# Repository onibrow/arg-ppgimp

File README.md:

# Arias Research Group - PPG & Impedence Measurement

## Seiya Ono Sp'19

The goal of this project is to collaborate with doctors at UCSD and Dr. Muller's student, Sina Faraji, to create a test bench for our group's Bioimpedence Array and OLED/OPD Oxymeter sensors to measure tissue damage in mice. We hope to use Sina Faraji's new OLED/OPD driver chip to take PPG measurements while using our own impedence arrays and electronics to measure tissue of the target.

-----

## Specs

- 1 PPG Sensor
    - 1 Red OLED
    - 1 NIR OLED
    - 1 OPD
    - Sina's Driver Chip
- 15 Impedence Electrodes
    - Impedence measurement AFE
    - Current Driver (200uA to 700uA, up to 1mA)
    - 15 to 2 selection mux
- 9V Power
- Coms over Serial

### PPG Sensor

Sina's OLED/OPD Driver Amplifier has the capability to driver 8 pairs of OLEDs and take readings from 8 OPDs. It handles all the amplification through SPI programmable registers. The closed loop in the transimpedence amplifiers can help get rid of any DC components in the OPD readings. It runs off of 1.1V digital logic, and 8V driver power.

If his chip does not go well, we will implement our own OLED drivers and OPD transimpedence amplifiers.

### Impedence Electrodes

We were asked to get our 15 electrode array to be able to take any impedence measurement between any two user selectable electrodes, while also being able to select any two electrodes to drive with a set amount of current. This divides this part of the board into three distance parts - the multiplexor selection and configuration, tunable current source, and impdence measurement. The following section will outline the different chip selection and their respective specs.

#### Multiplexor

Because the board is spec'd to be able to take impedence measurements as well as source current, it is critical to choose a multiplexor that has very low on resistance, while having very high off resistance. Luckily, most CMOS technology has this as standard, so picking an analog mux was not very difficult. We settled with the [ADG1608/1609](https://www.analog.com/en/products/adg1608.html) because of its 3 bit (8 input) mux, as well as its secondary variant 2 bit (4x2 input) DPDT (double pole double throw) configuration. To differentiate, the ADG1608 variant is the 3 bit 8 input mux, and the ADG1609 is the 2 bit 4x2 input mux. See the figure below for clarification.

By using two pairs of ADG1608's, a 16x2 input 1x2 output can be created. This means the circuit can individually select a pair of electrodes to be used by the impedence analyzer and tunable current source. To select between either of the two inputs, the ADG1609 will be used as a demuxer to select either the impedence analyzer or tunable current source. The DPDT configuration is very usedful in this sceneario because we are trying to always drive a _pair_ of electrodes. Here are some important specs when running off of a 3.3V power rail.

| Parameter | Value | Unit |
| --------- | ----- | ---- |
| R\_on      | 13.5  | Ohms |
| S/D Leakage | 0.1 | nA max |
| -3dB 1608 | 34 | MHz typ |
| -3dB 1609 | 72 | MHz typ |
| C\_S OFF | 23 | pF typ |
| C\_D OFF 1608 | 145 | pF type |
| C\_D OFF 1609 | 72 | pF typ |
| C\_S/D ON 1608 | 173 | pF typ |
| C\_S/D ON 1609 | 95 | pF typ |
| I\_DD | 0.001 | uA typ |
| V\_DD | 3.3 | V |
|I\_S/D 1608 | 126 | mA max |
|I\_S/D 1609 | 94 | mA max |

As we are dealing with specimens in the 10K Ohm range, the 13.5 Ohm and 173pF ON impedence is negligible, even if the electrode is traveling through 2 multiplexors. The max available current draw is much over the required 1mA of current through the electrodes, so the chip fits our needs. It aslo fits our impedance chip bandwidth, where it can do frequency sweeps over 1kHz to 100kHz. More on this in the "Impedence Analyzer" section.

#### Tunable Current Source

In order to drive our selectable electrodes with a user defined amount of current, we needed an adjustable current source. For this task, the [LM134/LM234/LM334 3-Terminal Adjustable Current Source](http://www.ti.com/product/LM134) was chosen. Specifically, the LM334 was chosen for its small form factor and easily identifiable 3-Pin Through Hole casing. It has a huge operating voltage from 1V to 40V, and can be tuned to supply current between 1uA to 10mA. The chip can also be operated in a temperature compensation region to eliminate its temperature dependence up to 0.2% accuracy.

For this circuit, the diode to use was already suggested, so the next choice was to pick out a digital potentiometer. TI also provided the math to prove the temperature coefficient compensation with the chosen diode, and drew the following relationship between R1 and R2:

From this, 1k and 10k 256 step digital potentiometers were chosen, with the math coming out to 3.9/39 Ohms per step, capable of driving in the range of 67.7uA to just short of 1mA. This just about fits our spec, going over to the upper limit of 1mA. The digital potentiometers chosen are the [AD8400](https://www.analog.com/en/products/ad8400.html) in both the 1K and 10K variant. They are controlled over SPI as designated write only slave devices. It can operate at between 3V and 5.5V and will typically draw less than 1mA.

#### Impedence Measurements

We would like to measure impedences between 1M Ohm (Magnitude) and 1k Ohm on our species. The chip for this is the [AD5933](https://www.analog.com/en/products/ad5933.html) which can do frequency sweeps. See Page 14 of the Data Sheet for more information on how to program the chip to do this.

Setting Gain - See Page 18 on how to choose the Gain setting resistor R\_FB to ensure that the analog readings do not saturate. The gain factor needs to be recalculated if R\_FB changes, if the output excitation voltage (more on this later) changes, or if the PGA gain is set differently. On the topic of operating voltages, there are 4 to choose from:

| Range | Output Excitation Voltage Amplitude | Output DC Bias Level | Output Series Resistance |
| ----- | ----------------------------------- | -------------------- | ------------------------ |
| 1 | 1.98 V p-p | 1.48 V | 200 Ohm |
| 2 | 0.97 V p-p | 0.76 V | 2.4k Ohm |
| 3 | 383 mV p-p | 0.31 V | 1.0k Ohm |
| 4 | 198 mV p-p | 0.173 V| 600 Ohm |

These numbers factor into what value should be chosen for the feedback resistor. The equation for choosing the feedback resistor is as follows:

Output Excitation Voltage Range * Gain Setting Resistor / Z\_Uknown * PGA Gain

By selecting the typical range 1 (~2V p-p) setting, we must choose a R\_FB that is roughly on the same order of magnitude as the unknown impedences we are measuring. From Yasser's Ulcer sensing paper (Swisher, S. L. et al. Impedance sensing device enables early detection of pressure ulcers in vivo. Nat. Commun. 6:6575 doi: 10.1038/ncomms7575 (2015)), we find that the typical impedence magnitude ranges from 10^4 to 10^6, so we will choos a 1M Ohm resistor for the feedback. This way, it should be able to cover a very wide range of impedences.

The chip does come with an internal 16.776 MHz oscillator, but it can be replaced by placing a 16MHz oscillator on MCLK, and then setting the control register to use the external clock. By default, on power up the internal oscillator is selected.

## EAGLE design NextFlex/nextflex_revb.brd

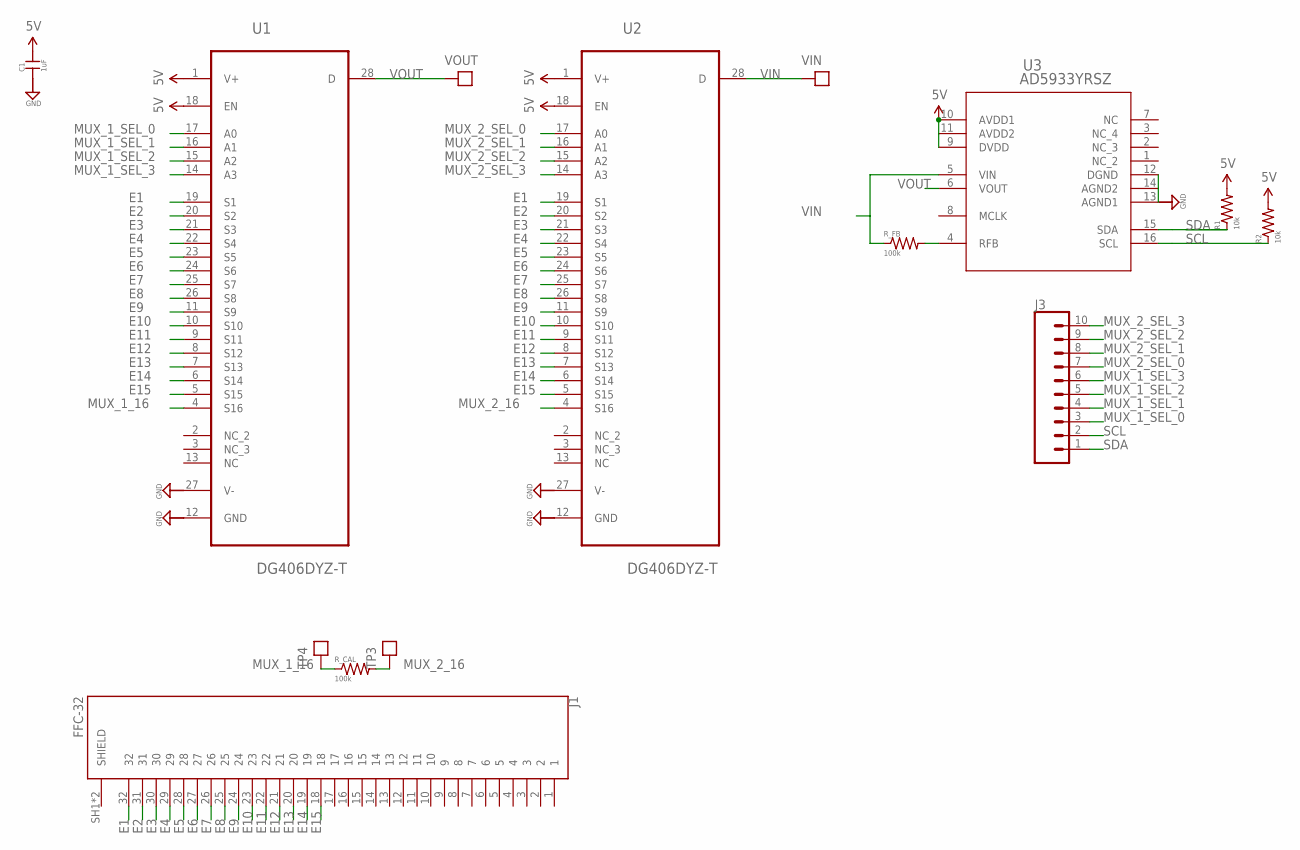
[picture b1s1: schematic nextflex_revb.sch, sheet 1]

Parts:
C1: 1uF; 0603-CAP
J1: FFC-32; MOLEX_503480-3200
J3: CONN_10"; 1X10
R1, R2: 10k; 0603-RES
R_CAL: 100k; 0603-RES
R_FB: 100k; 0603-RES
TP3, TP4: TEST_POINTTHRU; TEST_POINT
U1, U2: DG406DYZ-T; SOIC127P1032X265-28N
U3: AD5933YRSZ; RS_16
VIN: TEST_POINTTHRU; TEST_POINT
VOUT: TEST_POINTTHRU; TEST_POINT

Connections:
5V: C1.2, R1.2, R2.2, U1.1 (V+), U1.18 (EN), U2.1 (V+), U2.18 (EN), U3.9 (DVDD), U3.10 (AVDD1), U3.11 (AVDD2); also elsewhere on the board
E1: J1.32, U1.19 (S1), U2.19 (S1)
E2: J1.31, U1.20 (S2), U2.20 (S2)
E3: J1.30, U1.21 (S3), U2.21 (S3)
E4: J1.29, U1.22 (S4), U2.22 (S4)
E5: J1.28, U1.23 (S5), U2.23 (S5)
E6: J1.27, U1.24 (S6), U2.24 (S6)
E7: J1.26, U1.25 (S7), U2.25 (S7)
E8: J1.25, U1.26 (S8), U2.26 (S8)
E9: J1.24, U1.11 (S9), U2.11 (S9)
E10: J1.23, U1.10 (S10), U2.10 (S10)
E11: J1.22, U1.9 (S11), U2.9 (S11)
E12: J1.21, U1.8 (S12), U2.8 (S12)
E13: J1.20, U1.7 (S13), U2.7 (S13)
E14: J1.19, U1.6 (S14), U2.6 (S14)
E15: J1.18, U1.5 (S15), U2.5 (S15)
GND: C1.1, U1.12 (GND), U1.27 (V-), U2.12 (GND), U2.27 (V-), U3.12 (DGND), U3.13 (AGND1), U3.14 (AGND2); also elsewhere on the board
MUX_1_16: R_CAL.1, TP4.1, U1.4 (S16)
MUX_1_SEL_0: J3.3, U1.17 (A0); also elsewhere on the board
MUX_1_SEL_1: J3.4, U1.16 (A1); also elsewhere on the board
MUX_1_SEL_2: J3.5, U1.15 (A2); also elsewhere on the board
MUX_1_SEL_3: J3.6, U1.14 (A3); also elsewhere on the board
MUX_2_16: R_CAL.2, TP3.1, U2.4 (S16)
MUX_2_SEL_0: J3.7, U2.17 (A0); also elsewhere on the board
MUX_2_SEL_1: J3.8, U2.16 (A1); also elsewhere on the board
MUX_2_SEL_2: J3.9, U2.15 (A2); also elsewhere on the board
MUX_2_SEL_3: J3.10, U2.14 (A3); also elsewhere on the board
unnamed: R_FB.2, U3.4 (RFB)
SCL: J3.2, R2.1, U3.16 (SCL); also elsewhere on the board
SDA: J3.1, R1.1, U3.15 (SDA); also elsewhere on the board
VIN: R_FB.1, U2.28 (D), U3.5 (VIN), VIN.1
VOUT: U1.28 (D), U3.6 (VOUT), VOUT.1

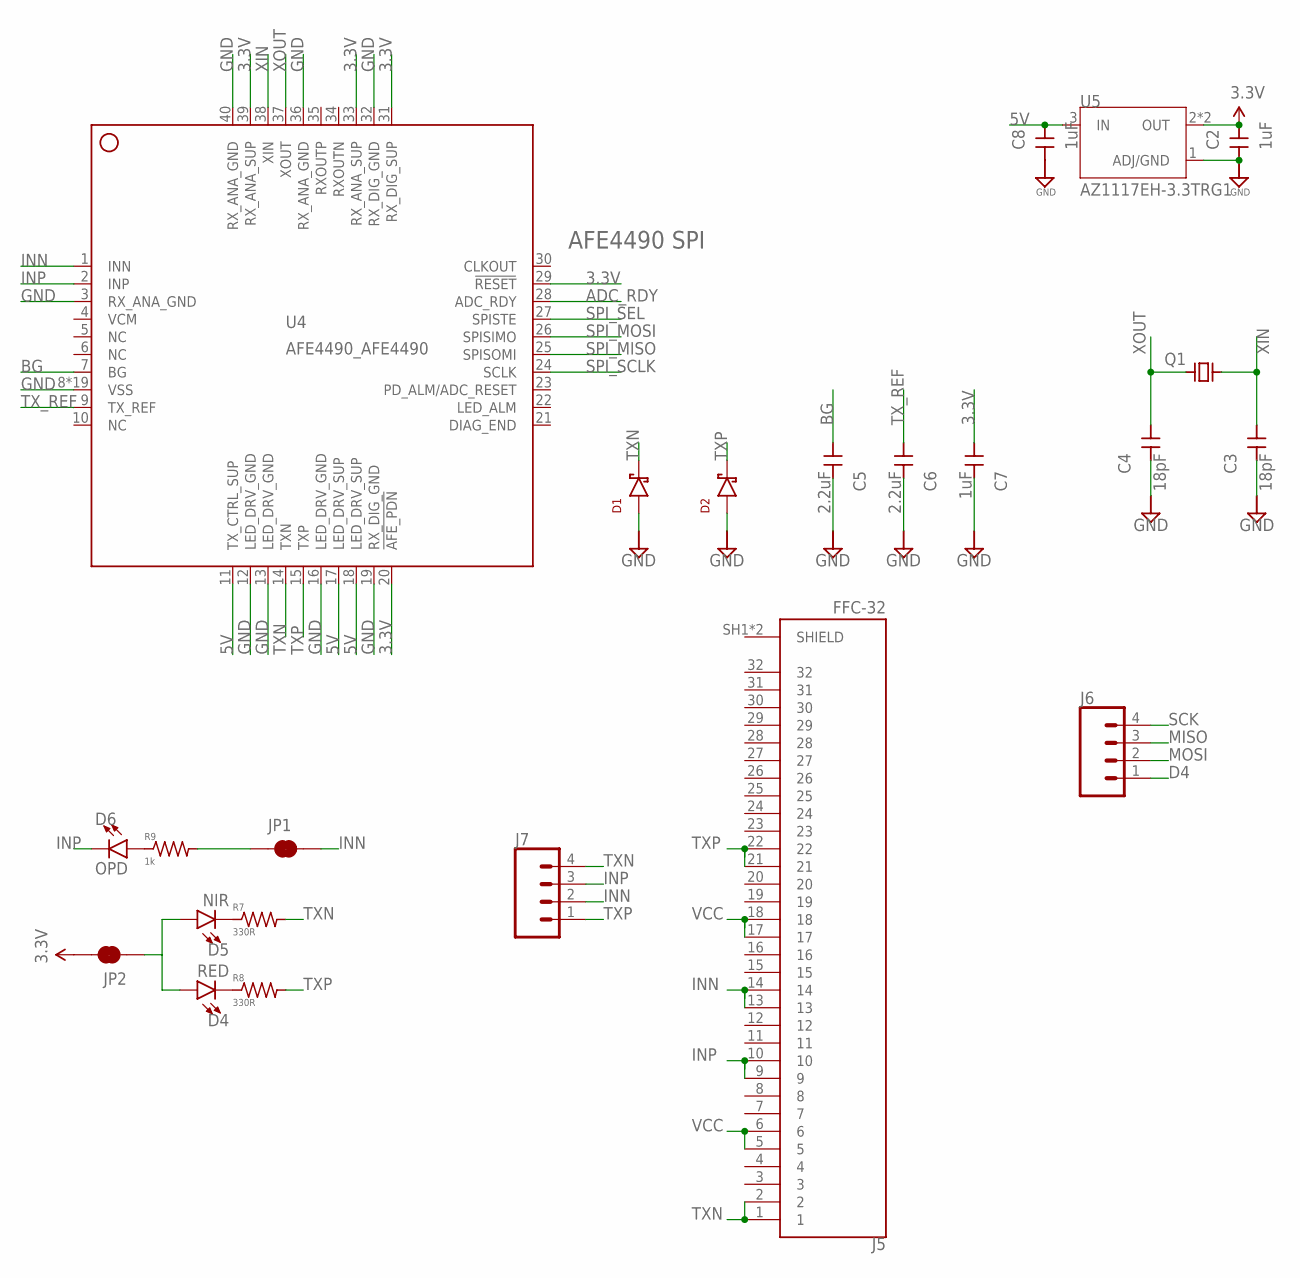
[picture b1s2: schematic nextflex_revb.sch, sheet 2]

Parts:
C2, C7, C8: 1uF; 0603-CAP
C3, C4: 18pF; 0603-CAP
C5, C6: 2.2uF; 0603-CAP
D1, D2: DIODE_CZRU; CZRU
D4: RED; LED-0603
D5: NIR; LED-0603
D6: OPD; LED-1206
J5: FFC-32; MOLEX_503480-3200
J6, J7: CONN_04; 1X04
JP1, JP2: JUMPER-SMT_2_NC_TRACE_NO-SILK; SMT-JUMPER_2_NC_TRACE_NO-SILK
Q1: CRYSTAL_SMOL; XTAL500X320X130N
R7, R8: 330R; 0603-RES
R9: 1k; 0603-RES
U4: AFE4490_AFE4490; AFE4490_QFN40-6X6
U5: AZ1117EH-3.3TRG1; SOT230P700X180-4N

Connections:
3.3V: C2.1, C7.1, JP2.2, U4.20 (!AFE_PDN), U4.29 (!RESET), U4.31 (RX_DIG_SUP), U4.33 (RX_ANA_SUP), U4.39 (RX_ANA_SUP), U5.2 (OUT), U5.4 (OUT); also elsewhere on the board
5V: C8.1, U4.11 (TX_CTRL_SUP), U4.17 (LED_DRV_SUP), U4.18 (LED_DRV_SUP), U5.3 (IN); also elsewhere on the board
ADC_RDY: U4.28 (ADC_RDY)
BG: C5.1, U4.7 (BG)
D4: J6.1; also elsewhere on the board
GND: C2.2, C3.2, C4.2, C5.2, C6.2, C7.2, C8.2, D1.P, D2.P, U4.3 (RX_ANA_GND), U4.8 (VSS), U4.12 (LED_DRV_GND), U4.13 (LED_DRV_GND), U4.16 (LED_DRV_GND), U4.19 (RX_DIG_GND), U4.32 (RX_DIG_GND), U4.36 (RX_ANA_GND), U4.40 (RX_ANA_GND), U4.EXP@1 (VSS), U4.EXP@2 (VSS), U4.EXP@3 (VSS), U4.EXP@4 (VSS), U4.EXP@5 (VSS), U4.EXP@6 (VSS), U4.EXP@7 (VSS), U4.EXP@8 (VSS), U4.EXP@9 (VSS), U4.EXP@10 (VSS), U4.EXP@11 (VSS), U4.EXP@12 (VSS), U4.EXP@13 (VSS), U4.EXP@14 (VSS), U4.EXP@15 (VSS), U4.EXP@16 (VSS), U4.PWR@1 (VSS), U4.PWR@2 (VSS), U5.1 (ADJ/GND); also elsewhere on the board
INN: J5.13, J5.14, J7.2, JP1.2, U4.1 (INN)
INP: D6.C, J5.9, J5.10, J7.3, U4.2 (INP)
MISO: J6.3; also elsewhere on the board
MOSI: J6.2; also elsewhere on the board
unnamed: D4.A, D5.A, JP2.1
unnamed: D5.C, R7.1
unnamed: D4.C, R8.1
unnamed: D6.A, R9.1
unnamed: JP1.1, R9.2
SCK: J6.4; also elsewhere on the board
SPI_MISO: U4.25 (SPISOMI); also elsewhere on the board
SPI_MOSI: U4.26 (SPISIMO); also elsewhere on the board
SPI_SCLK: U4.24 (SCLK); also elsewhere on the board
SPI_SEL: U4.27 (SPISTE); also elsewhere on the board
TXN: D1.N, J5.1, J5.2, J7.4, R7.2, U4.14 (TXN)
TXP: D2.N, J5.21, J5.22, J7.1, R8.2, U4.15 (TXP)
TX_REF: C6.1, U4.9 (TX_REF)
VCC: J5.5, J5.6, J5.17, J5.18; also elsewhere on the board
XIN: C3.1, Q1.1 (A), U4.38 (XIN)
XOUT: C4.1, Q1.2 (B), U4.37 (XOUT)

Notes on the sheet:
AFE4490 SPI

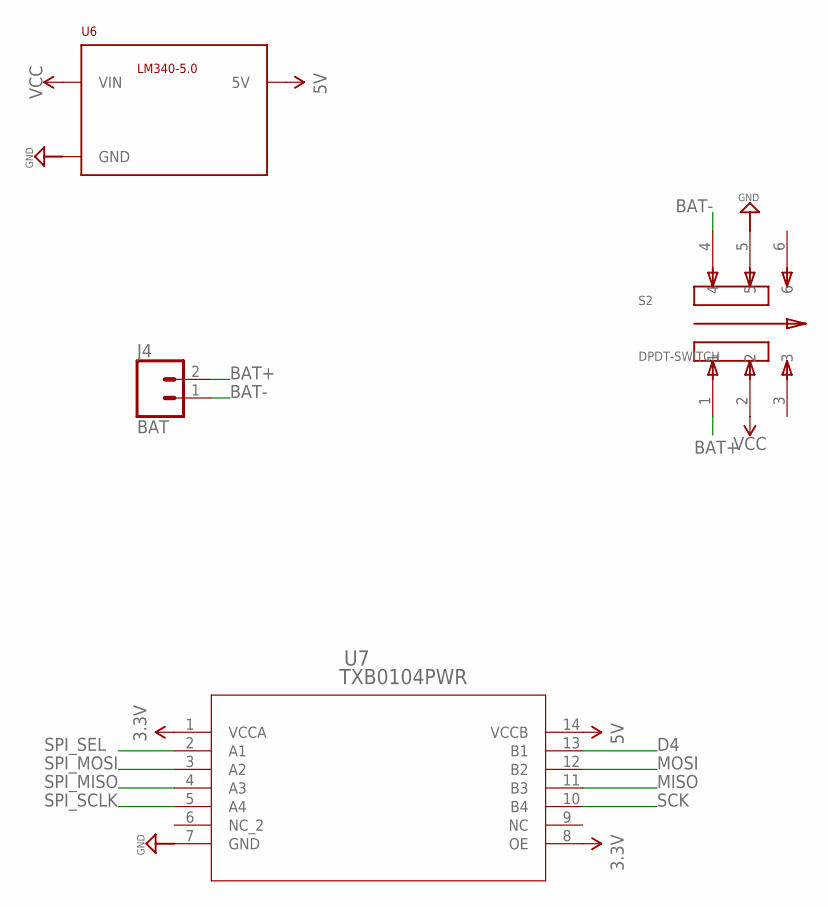
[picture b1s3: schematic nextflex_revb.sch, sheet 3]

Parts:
J4: BAT; 1X02
S2: DPDT-SWITCH; SW_JS202011SCQN
U6: LM340MPX-5.0230; SOT230P700X180-4N
U7: TXB0104PWR; PW14

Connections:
3.3V: U7.1 (VCCA), U7.8 (OE); also elsewhere on the board
5V: U6.3 (5V), U7.14 (VCCB); also elsewhere on the board
BAT+: J4.2, S2.1
BAT-: J4.1, S2.4
D4: U7.13 (B1); also elsewhere on the board
GND: S2.5, U6.2 (GND), U6.4 (GND), U7.7 (GND); also elsewhere on the board
MISO: U7.11 (B3); also elsewhere on the board
MOSI: U7.12 (B2); also elsewhere on the board
SCK: U7.10 (B4); also elsewhere on the board
SPI_MISO: U7.4 (A3); also elsewhere on the board
SPI_MOSI: U7.3 (A2); also elsewhere on the board
SPI_SCLK: U7.5 (A4); also elsewhere on the board
SPI_SEL: U7.2 (A1); also elsewhere on the board
VCC: S2.2, U6.1 (VIN); also elsewhere on the board

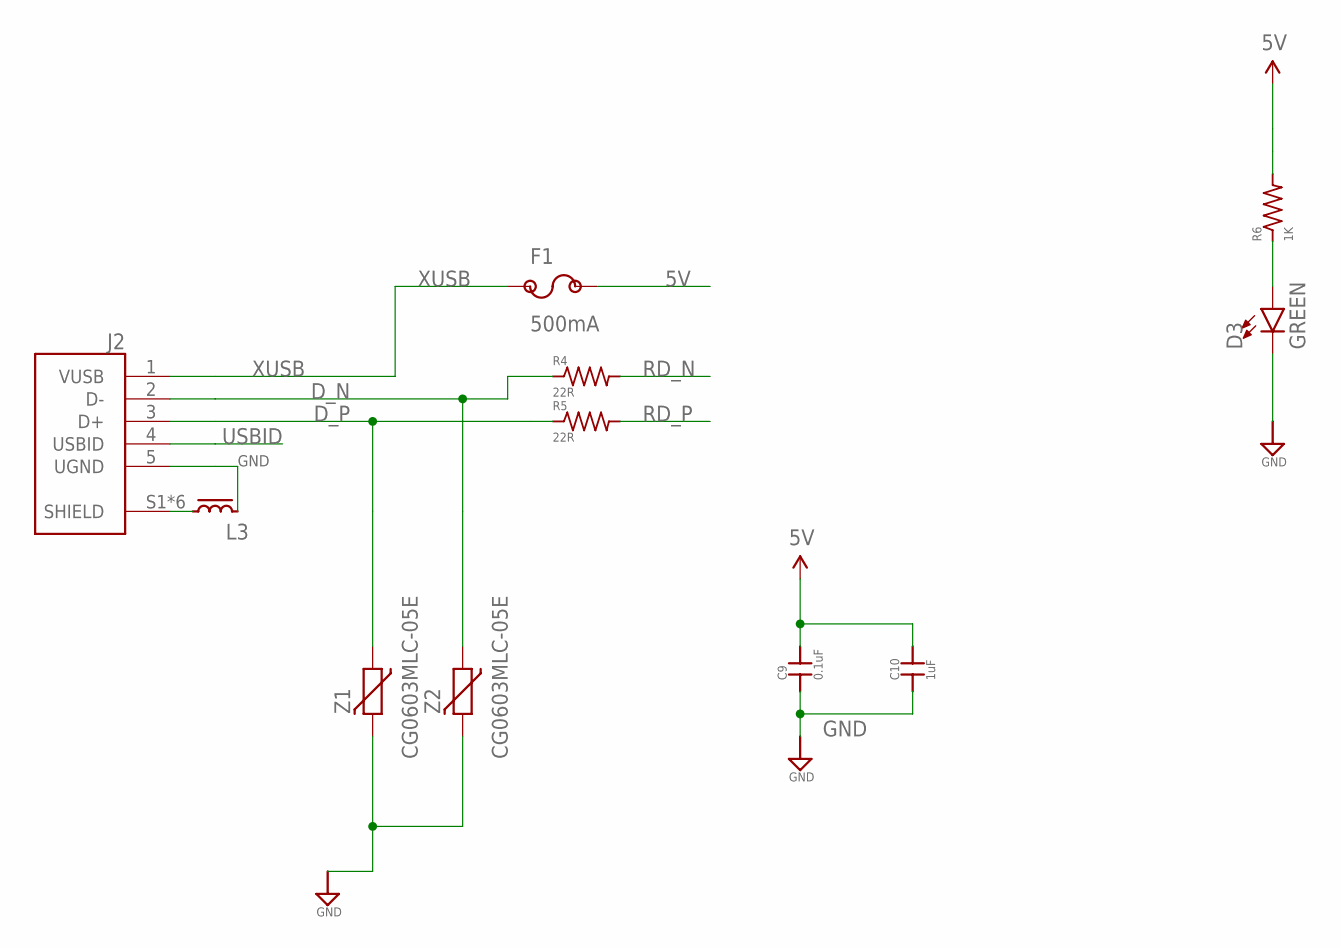
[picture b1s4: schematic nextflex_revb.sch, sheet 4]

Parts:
C9: 0.1uF; 0603-CAP
C10: 1uF; 0603-CAP
D3: GREEN; LED-0603
F1: 500mA; 1206
J2: USB; FCI_10103594-0001LF
L3: IND; IND_2012
R4, R5: 22R; 0603-RES
R6: 1K; 0603-RES
Z1, Z2: CG0603MLC-05E; 0603-RES

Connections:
5V: C9.2, C10.2, F1.2, R6.2; also elsewhere on the board
D_N: J2.2 (D-), R4.1, Z2.1
D_P: J2.3 (D+), R5.1, Z1.1
GND: C9.1, C10.1, D3.C, J2.5 (UGND), L3.2, Z1.2, Z2.2; also elsewhere on the board
unnamed: D3.A, R6.1
RD_N: R4.2; also elsewhere on the board
RD_P: R5.2; also elsewhere on the board
SHIELD: J2.S1 (SHIELD), J2.S2 (SHIELD), J2.S3 (SHIELD), J2.S4 (SHIELD), J2.S5 (SHIELD), J2.S6 (SHIELD), L3.1
USBID: J2.4 (USBID)
XUSB: F1.1, J2.1 (VUSB)

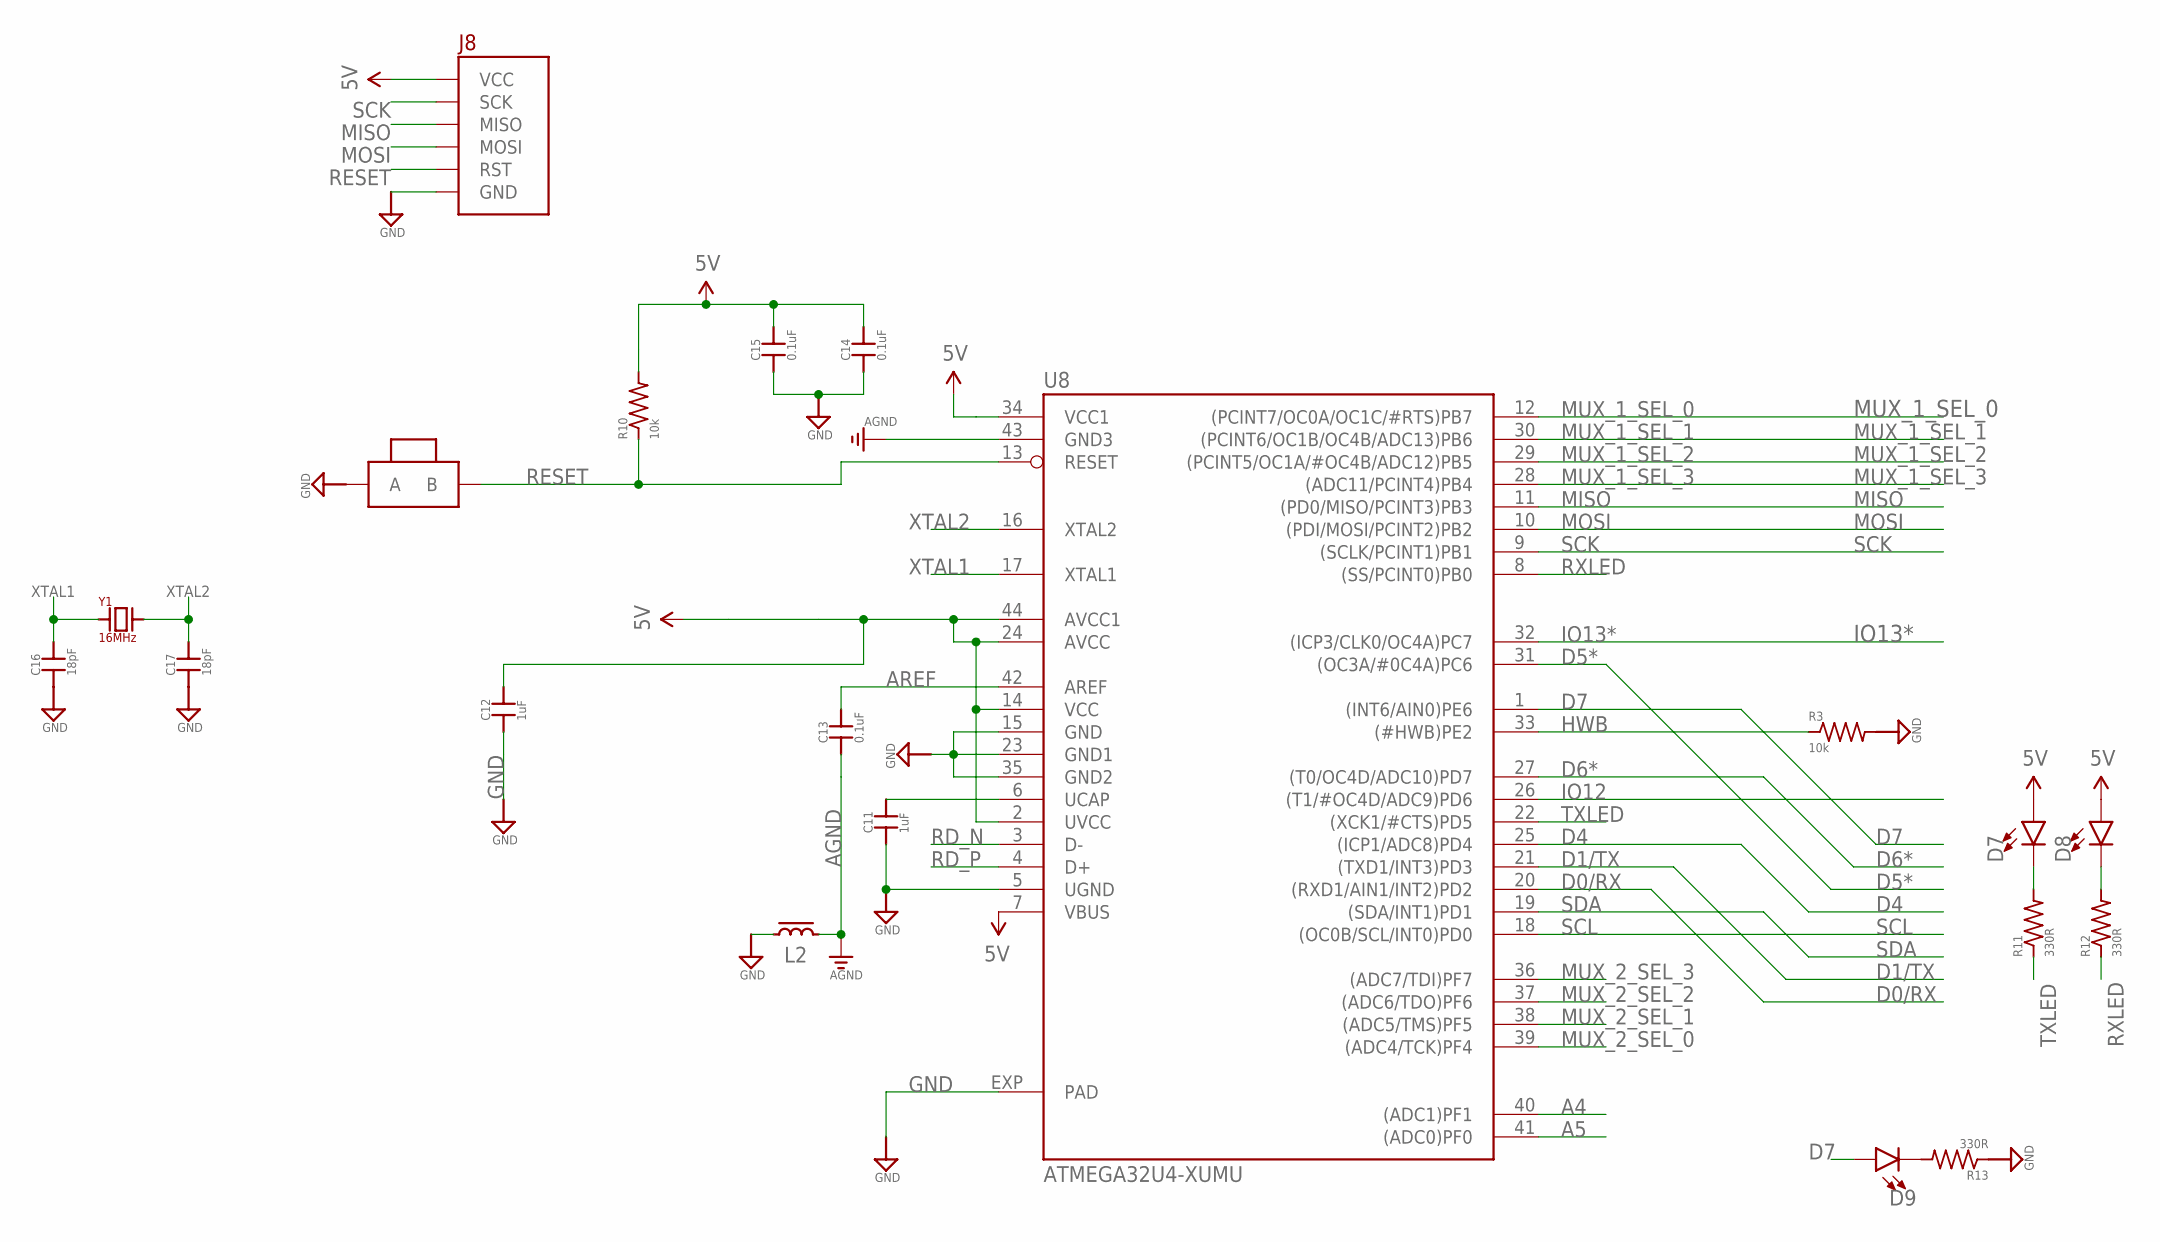
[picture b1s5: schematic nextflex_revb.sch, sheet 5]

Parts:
C11, C12: 1uF; 0603-CAP
C13, C14, C15: 0.1uF; 0603-CAP
C16, C17: 18pF; 0603-CAP
D7, D8, D9: LED0603; LED-0603
J8: BURNIN
L2: IND; IND_2012
R3, R10: 10k; 0603-RES
R11, R12, R13: 330R; 0603-RES
SW1: BTN-PTS810; BTN_PTS810
U8: ATMEGA32U4-XUMU; QFN44ML7X7
Y1: 16MHz; XTAL500X320X130N

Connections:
5V: C12.2, C14.2, C15.2, D7.A, D8.A, J8.3.3V (VCC), R10.2, U8.2 (UVCC), U8.7 (VBUS), U8.14 (VCC), U8.24 (AVCC), U8.34 (VCC1), U8.44 (AVCC1); also elsewhere on the board
A4: U8.40 ((ADC1)PF1)
A5: U8.41 ((ADC0)PF0)
AGND: C13.1, L2.2, U8.43 (GND3)
AREF: C13.2, U8.42 (AREF)
D0/RX: U8.20 ((RXD1/AIN1/INT2)PD2)
D1/TX: U8.21 ((TXD1/INT3)PD3)
D4: U8.25 ((ICP1/ADC8)PD4); also elsewhere on the board
D5*: U8.31 ((OC3A/#0C4A)PC6)
D6*: U8.27 ((T0/OC4D/ADC10)PD7)
D7: D9.A, U8.1 ((INT6/AIN0)PE6)
GND: C11.1, C12.1, C14.1, C15.1, C16.1, C17.1, J8.GND, L2.1, R3.2, R13.1, SW1.1 (A), SW1.2 (A), U8.5 (UGND), U8.15 (GND), U8.23 (GND1), U8.35 (GND2), U8.EXP (PAD); also elsewhere on the board
HWB: R3.1, U8.33 ((#HWB)PE2)
IO12: U8.26 ((T1/#OC4D/ADC9)PD6)
IO13*: U8.32 ((ICP3/CLK0/OC4A)PC7)
MISO: J8.MISO, U8.11 ((PD0/MISO/PCINT3)PB3); also elsewhere on the board
MOSI: J8.MOSI, U8.10 ((PDI/MOSI/PCINT2)PB2); also elsewhere on the board
MUX_1_SEL_0: U8.12 ((PCINT7/OC0A/OC1C/#RTS)PB7); also elsewhere on the board
MUX_1_SEL_1: U8.30 ((PCINT6/OC1B/OC4B/ADC13)PB6); also elsewhere on the board
MUX_1_SEL_2: U8.29 ((PCINT5/OC1A/#OC4B/ADC12)PB5); also elsewhere on the board
MUX_1_SEL_3: U8.28 ((ADC11/PCINT4)PB4); also elsewhere on the board
MUX_2_SEL_0: U8.39 ((ADC4/TCK)PF4); also elsewhere on the board
MUX_2_SEL_1: U8.38 ((ADC5/TMS)PF5); also elsewhere on the board
MUX_2_SEL_2: U8.37 ((ADC6/TDO)PF6); also elsewhere on the board
MUX_2_SEL_3: U8.36 ((ADC7/TDI)PF7); also elsewhere on the board
unnamed: D7.C, R11.2
unnamed: D8.C, R12.2
unnamed: D9.C, R13.2
RD_N: U8.3 (D-); also elsewhere on the board
RD_P: U8.4 (D+); also elsewhere on the board
RESET: J8.RST, R10.1, SW1.3 (B), SW1.4 (B), U8.13 (RESET)
RXLED: R12.1, U8.8 ((SS/PCINT0)PB0)
SCK: J8.SCK, U8.9 ((SCLK/PCINT1)PB1); also elsewhere on the board
SCL: U8.18 ((OC0B/SCL/INT0)PD0); also elsewhere on the board
SDA: U8.19 ((SDA/INT1)PD1); also elsewhere on the board
TXLED: R11.1, U8.22 ((XCK1/#CTS)PD5)
UCAP: C11.2, U8.6 (UCAP)
XTAL1: C16.2, U8.17 (XTAL1), Y1.1 (A)
XTAL2: C17.2, U8.16 (XTAL2), Y1.2 (B)

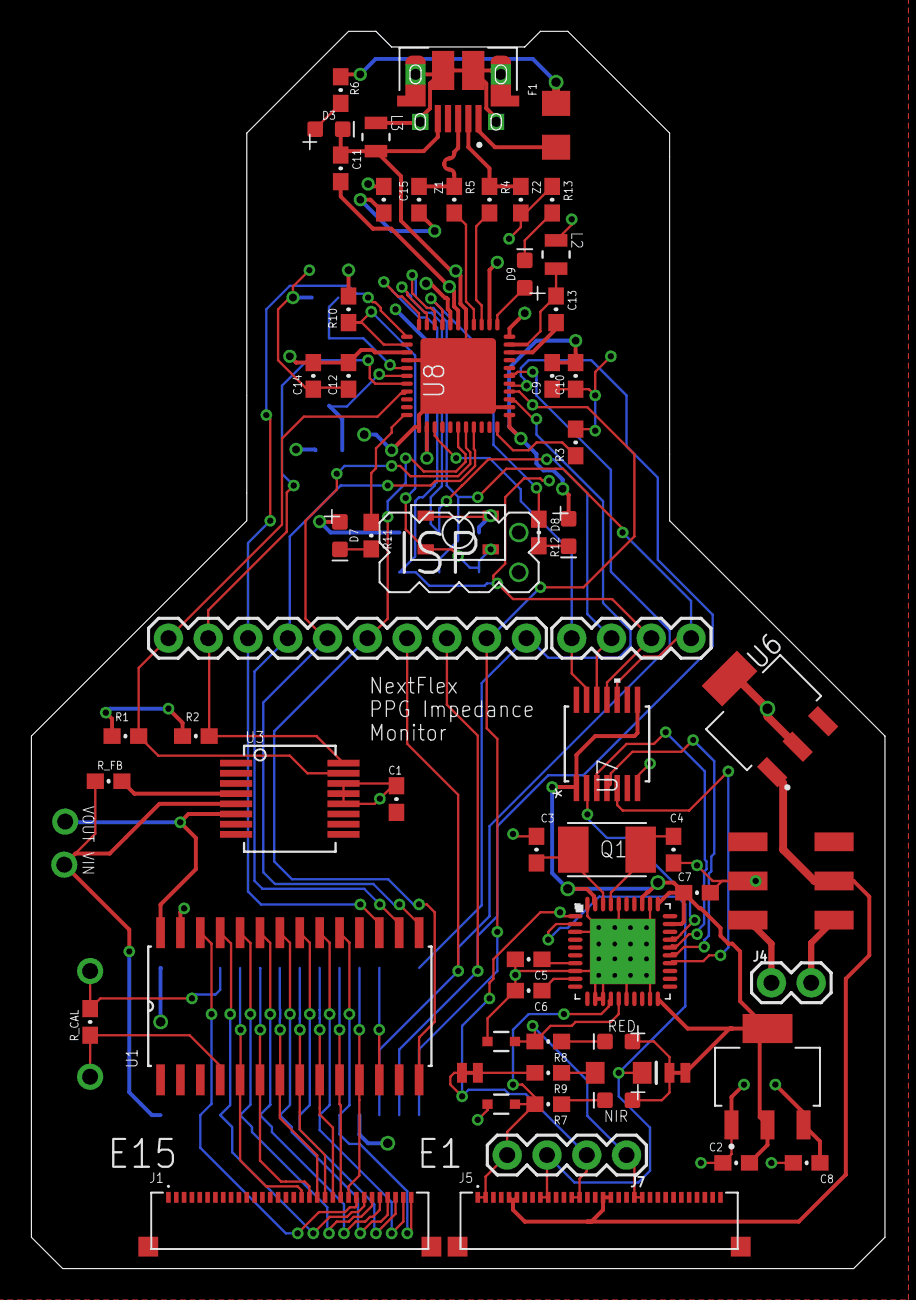
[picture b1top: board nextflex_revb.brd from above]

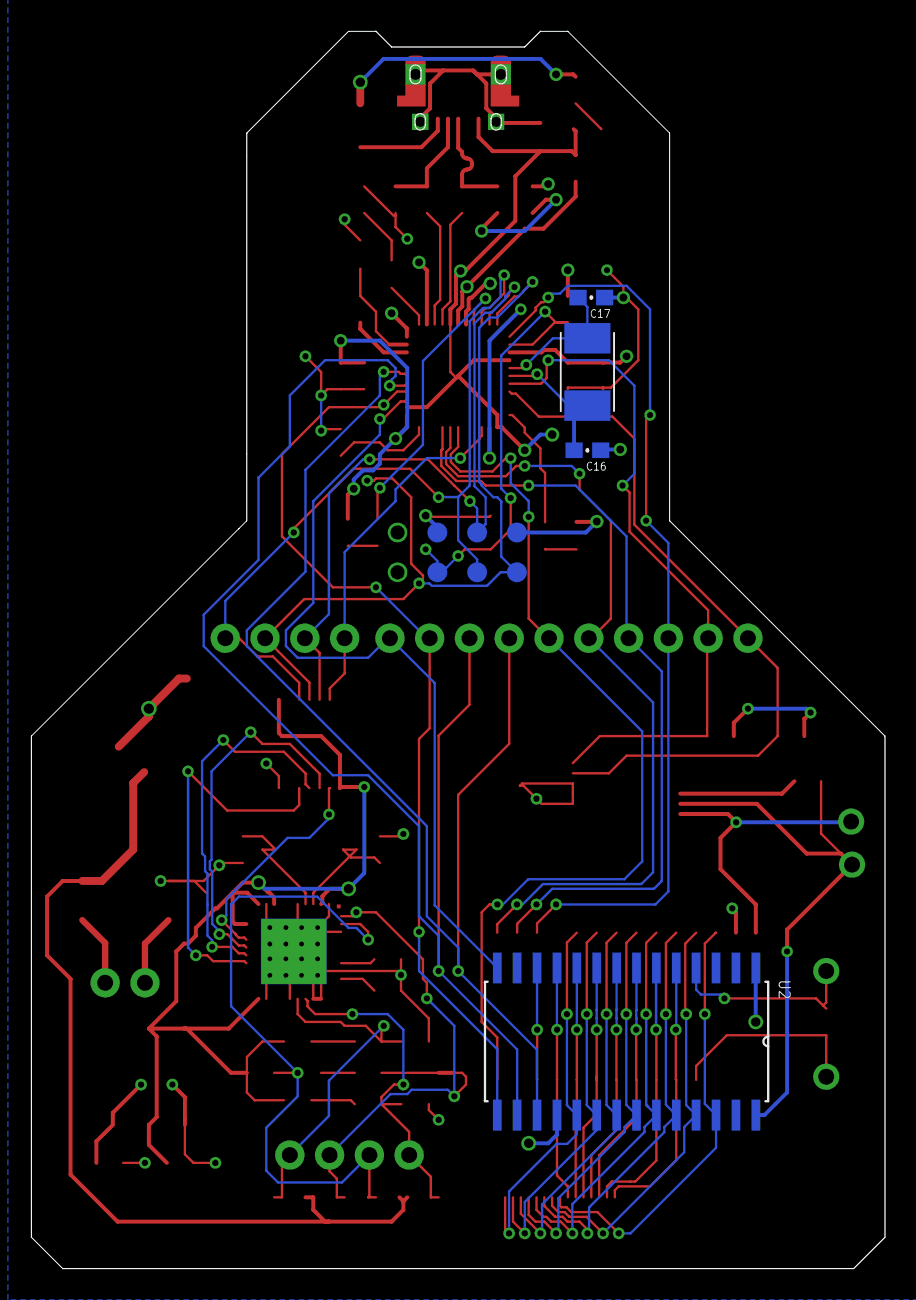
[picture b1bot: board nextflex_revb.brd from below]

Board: 2 copper layers, 54.5 x 79.0 mm, 72 parts (4 on the bottom side), 77 nets.

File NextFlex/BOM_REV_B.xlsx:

Comment | Designator | Footprint | LCSC Part #（optional）
0.1uF | C9, C13, C14, C15 | 0603_C | C14663
1uF | C1, C2, C7, C8, C10, C11, C12 | 0603_C | C15849
18pF | C3, C4 | 0603_C | C1647
2.2uF | C5, C6 | 0603_C | C23630
10k | R1, R2, R3, R10 | 0603_R | C25804
22 | R4, R5 | 0603_R | C23345
330 | R7, R8, R11, R12, R13 | 0603_R | C23138
1k | R6, R9 | 0603_R | C21190
100k | R_CAL, R_FB | 0603_R | C25803
ATMEGA32U4 | U8 | QFN-44_EP_7x7x0.5P | C112161
Green | D3, D5 | LED_0603 | C72043
Red | D4, D7, D8, D9 | LED_0603 | C2286

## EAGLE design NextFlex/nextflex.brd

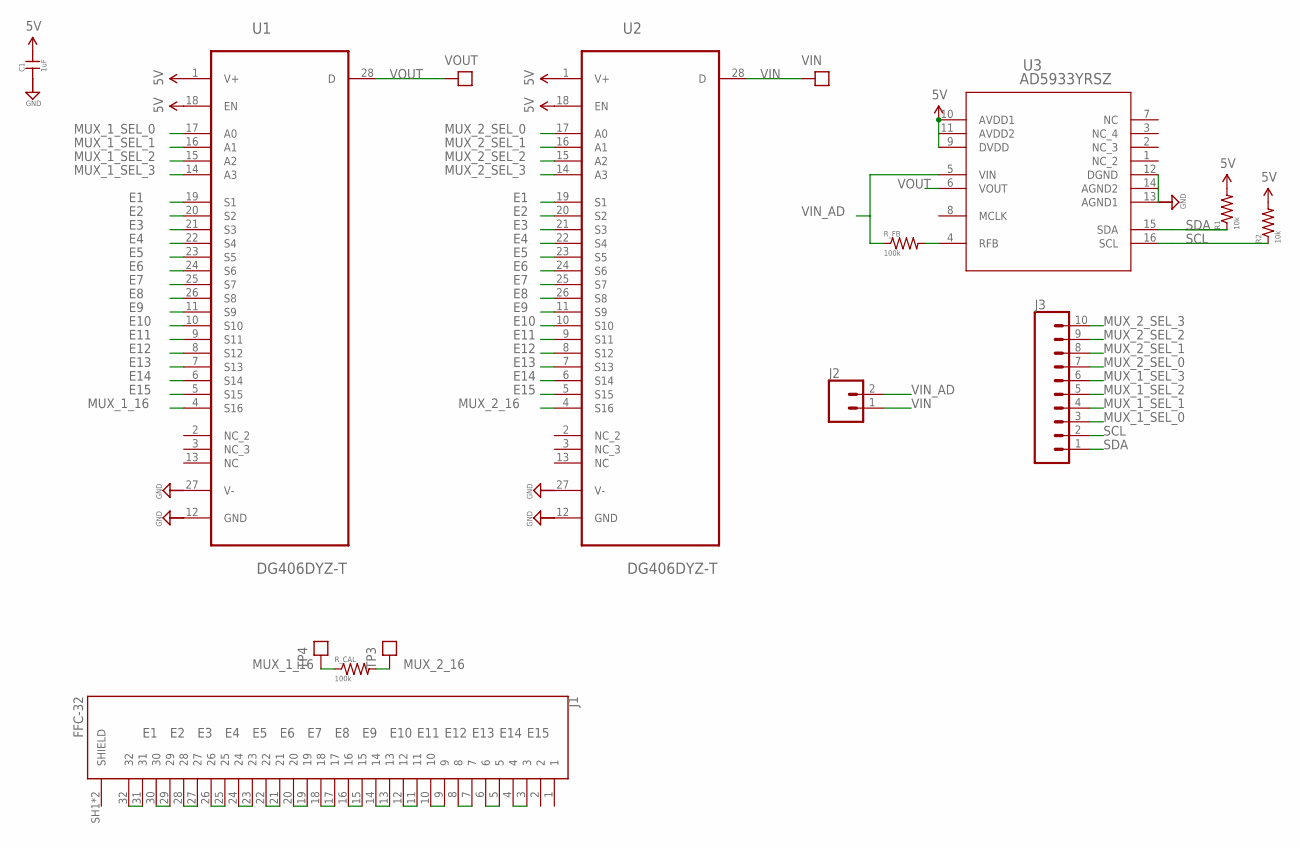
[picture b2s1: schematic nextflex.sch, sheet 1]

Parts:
C1: 1uF; 0603-CAP
J1: FFC-32; MOLEX_503480-3200
J2: CONN_02; 1X02
J3: CONN_10"; 1X10
R1, R2: 10k; 0603-RES
R_CAL: 100k; 0603-RES
R_FB: 100k; 0603-RES
TP3, TP4: TEST_POINTTHRU; TEST_POINT
U1, U2: DG406DYZ-T; SOIC127P1032X265-28N
U3: AD5933YRSZ; RS_16
VIN: TEST_POINTTHRU; TEST_POINT
VOUT: TEST_POINTTHRU; TEST_POINT

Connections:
5V: C1.2, R1.2, R2.2, U1.1 (V+), U1.18 (EN), U2.1 (V+), U2.18 (EN), U3.9 (DVDD), U3.10 (AVDD1), U3.11 (AVDD2); also elsewhere on the board
E1: J1.31, J1.32, U1.19 (S1), U2.19 (S1)
E2: J1.29, J1.30, U1.20 (S2), U2.20 (S2)
E3: J1.27, J1.28, U1.21 (S3), U2.21 (S3)
E4: J1.25, J1.26, U1.22 (S4), U2.22 (S4)
E5: J1.23, J1.24, U1.23 (S5), U2.23 (S5)
E6: J1.21, J1.22, U1.24 (S6), U2.24 (S6)
E7: J1.19, J1.20, U1.25 (S7), U2.25 (S7)
E8: J1.17, J1.18, U1.26 (S8), U2.26 (S8)
E9: J1.15, J1.16, U1.11 (S9), U2.11 (S9)
E10: J1.13, J1.14, U1.10 (S10), U2.10 (S10)
E11: J1.11, J1.12, U1.9 (S11), U2.9 (S11)
E12: J1.9, J1.10, U1.8 (S12), U2.8 (S12)
E13: J1.7, J1.8, U1.7 (S13), U2.7 (S13)
E14: J1.5, J1.6, U1.6 (S14), U2.6 (S14)
E15: J1.3, J1.4, U1.5 (S15), U2.5 (S15)
GND: C1.1, U1.12 (GND), U1.27 (V-), U2.12 (GND), U2.27 (V-), U3.12 (DGND), U3.13 (AGND1), U3.14 (AGND2); also elsewhere on the board
MUX_1_16: R_CAL.1, TP4.1, U1.4 (S16)
MUX_1_SEL_0: J3.3, U1.17 (A0)
MUX_1_SEL_1: J3.4, U1.16 (A1)
MUX_1_SEL_2: J3.5, U1.15 (A2)
MUX_1_SEL_3: J3.6, U1.14 (A3)
MUX_2_16: R_CAL.2, TP3.1, U2.4 (S16)
MUX_2_SEL_0: J3.7, U2.17 (A0)
MUX_2_SEL_1: J3.8, U2.16 (A1)
MUX_2_SEL_2: J3.9, U2.15 (A2)
MUX_2_SEL_3: J3.10, U2.14 (A3)
unnamed: R_FB.2, U3.4 (RFB)
SCL: J3.2, R2.1, U3.16 (SCL)
SDA: J3.1, R1.1, U3.15 (SDA)
VIN: J2.1, U2.28 (D), VIN.1
VIN_AD: J2.2, R_FB.1, U3.5 (VIN)
VOUT: U1.28 (D), U3.6 (VOUT), VOUT.1

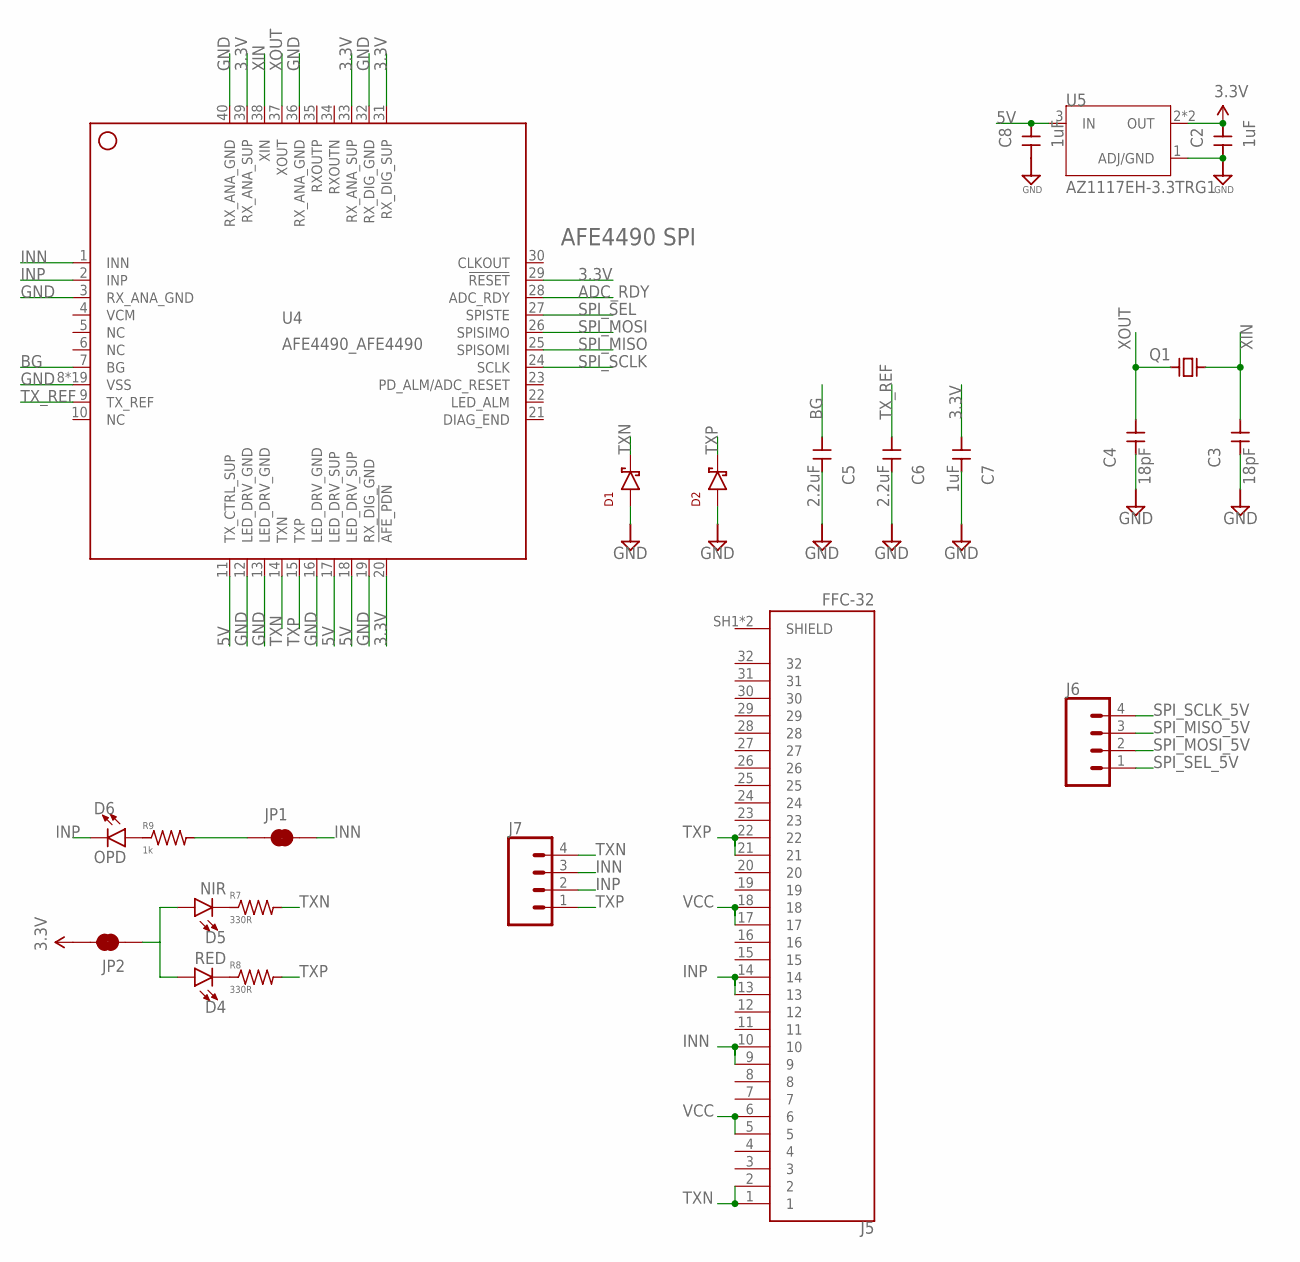
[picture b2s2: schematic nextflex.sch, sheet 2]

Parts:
C2, C7, C8: 1uF; 0603-CAP
C3, C4: 18pF; 0603-CAP
C5, C6: 2.2uF; 0603-CAP
D1, D2: DIODE_CZRU; CZRU
D4: RED; LED-0603
D5: NIR; LED-0603
D6: OPD; LED-1206
J5: FFC-32; MOLEX_503480-3200
J6, J7: CONN_04; 1X04
JP1, JP2: JUMPER-SMT_2_NC_TRACE_NO-SILK; SMT-JUMPER_2_NC_TRACE_NO-SILK
Q1: CRYSTAL_SMOL; XTAL500X320X130N
R7, R8: 330R; 0603-RES
R9: 1k; 0603-RES
U4: AFE4490_AFE4490; AFE4490_QFN40-6X6
U5: AZ1117EH-3.3TRG1; SOT230P700X180-4N

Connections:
3.3V: C2.1, C7.1, JP2.2, U4.20 (!AFE_PDN), U4.29 (!RESET), U4.31 (RX_DIG_SUP), U4.33 (RX_ANA_SUP), U4.39 (RX_ANA_SUP), U5.2 (OUT), U5.4 (OUT); also elsewhere on the board
5V: C8.1, U4.11 (TX_CTRL_SUP), U4.17 (LED_DRV_SUP), U4.18 (LED_DRV_SUP), U5.3 (IN); also elsewhere on the board
ADC_RDY: U4.28 (ADC_RDY)
BG: C5.1, U4.7 (BG)
GND: C2.2, C3.2, C4.2, C5.2, C6.2, C7.2, C8.2, D1.P, D2.P, U4.3 (RX_ANA_GND), U4.8 (VSS), U4.12 (LED_DRV_GND), U4.13 (LED_DRV_GND), U4.16 (LED_DRV_GND), U4.19 (RX_DIG_GND), U4.32 (RX_DIG_GND), U4.36 (RX_ANA_GND), U4.40 (RX_ANA_GND), U4.EXP@1 (VSS), U4.EXP@2 (VSS), U4.EXP@3 (VSS), U4.EXP@4 (VSS), U4.EXP@5 (VSS), U4.EXP@6 (VSS), U4.EXP@7 (VSS), U4.EXP@8 (VSS), U4.EXP@9 (VSS), U4.EXP@10 (VSS), U4.EXP@11 (VSS), U4.EXP@12 (VSS), U4.EXP@13 (VSS), U4.EXP@14 (VSS), U4.EXP@15 (VSS), U4.EXP@16 (VSS), U4.PWR@1 (VSS), U4.PWR@2 (VSS), U5.1 (ADJ/GND); also elsewhere on the board
INN: J5.9, J5.10, J7.3, JP1.2, U4.1 (INN)
INP: D6.C, J5.13, J5.14, J7.2, U4.2 (INP)
unnamed: D4.A, D5.A, JP2.1
unnamed: D5.C, R7.1
unnamed: D4.C, R8.1
unnamed: D6.A, R9.1
unnamed: JP1.1, R9.2
SPI_MISO: U4.25 (SPISOMI); also elsewhere on the board
SPI_MISO_5V: J6.3; also elsewhere on the board
SPI_MOSI: U4.26 (SPISIMO); also elsewhere on the board
SPI_MOSI_5V: J6.2; also elsewhere on the board
SPI_SCLK: U4.24 (SCLK); also elsewhere on the board
SPI_SCLK_5V: J6.4; also elsewhere on the board
SPI_SEL: U4.27 (SPISTE); also elsewhere on the board
SPI_SEL_5V: J6.1; also elsewhere on the board
TXN: D1.N, J5.1, J5.2, J7.4, R7.2, U4.14 (TXN)
TXP: D2.N, J5.21, J5.22, J7.1, R8.2, U4.15 (TXP)
TX_REF: C6.1, U4.9 (TX_REF)
VCC: J5.5, J5.6, J5.17, J5.18; also elsewhere on the board
XIN: C3.1, Q1.1 (A), U4.38 (XIN)
XOUT: C4.1, Q1.2 (B), U4.37 (XOUT)

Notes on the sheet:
AFE4490 SPI

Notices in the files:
parts and their libraries:
SparkFun-Connectors: Licensing: Creative Commons ShareAlike 4.0 International - https://creativecommons.org/licenses/by-sa/4.0
